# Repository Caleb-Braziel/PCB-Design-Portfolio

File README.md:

# PCB Design Portfolio

This repository contains a curated set of PCB design projects developed for instructional use and technical mentorship. The designs demonstrate practical workflows in schematic capture, hierarchical design, PCB layout, and manufacturability using KiCad and EAGLE.

While many of these projects were created for teaching purposes, they reflect real-world PCB design practices and increasing levels of technical complexity.

---

## Project Overview

The projects in this repository span a range of complexity, from introductory designs to advanced power and embedded systems.

### EAGLE Projects
- **Night Light PCB**  
  A fully fabricated PCB for a night light circuit, including LED and basic power components, laid out and soldered.

### KiCad Projects
- **AC to DC Converter**  
  An AC-DC power supply PCB circuit, designed for voltage conversion and basic power regulation.

- **DC Motor Speed Controller**  
  A PCB for controlling the speed of a DC motor, using discrete components and control circuitry.

- **GPS Tracker with STM32**  
  A microcontroller-based PCB integrating a GPS module for location tracking.

---

## Design Focus

Across these projects, the primary design goals include:
- Clear schematic organization and hierarchy
- Manufacturable PCB layouts
- Proper grounding and power distribution
- Debuggability and clarity for future modification
- Progressive increase in design complexity

---

## Tools & Technologies

- **EDA Tools:** KiCad, EAGLE  
- **Design Skills:** Schematic capture, hierarchical design, PCB layout, ERC/DRC validation  
- **Domains:** Power electronics, motor control, embedded systems  
- **Fabrication:** PCB manufacturing support and hand soldering (select projects)

---

## Notes

Some designs were developed as instructional examples and may not represent finalized commercial products. However, all projects follow industry-standard PCB design practices and are intended to demonstrate technical proficiency and design intent.

---

## Author

Caleb Braziel  
Mechanical Engineering / Embedded & PCB Design

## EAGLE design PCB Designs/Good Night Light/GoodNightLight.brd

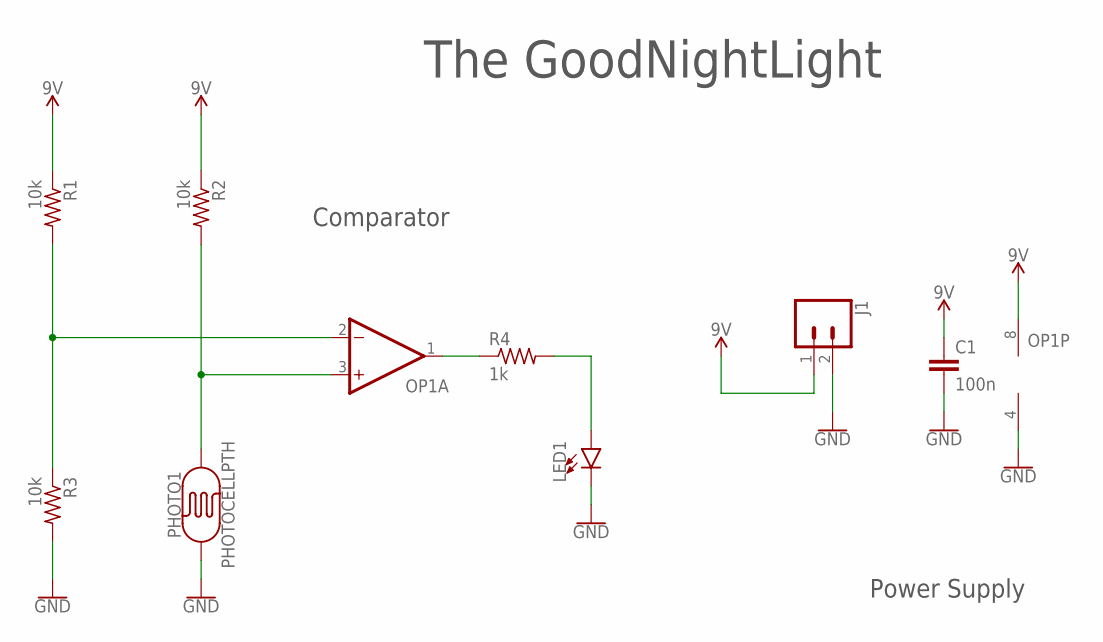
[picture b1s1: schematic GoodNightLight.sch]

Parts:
C1: 100n; C0603
J1: CONN_02; 1X02
LED1: LED5MM; LED_5MM
OP1: OP-DUALR; SO8
PHOTO1: PHOTOCELLPTH; PHOTOCELL
R1, R2, R3: 10k; R0603
R4: 1k; R0603

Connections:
9V: C1.1, J1.1, OP1.8 (V+), R1.1, R2.1
GND: C1.2, J1.2, LED1.K (C), OP1.4 (V-), PHOTO1.1, R3.2
unnamed: OP1.3 (+IN), PHOTO1.2, R2.2
unnamed: OP1.1 (OUT), R4.1
unnamed: OP1.2 (-IN), R1.2, R3.1
unnamed: LED1.A, R4.2

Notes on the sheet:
The GoodNightLight
Comparator
Power Supply

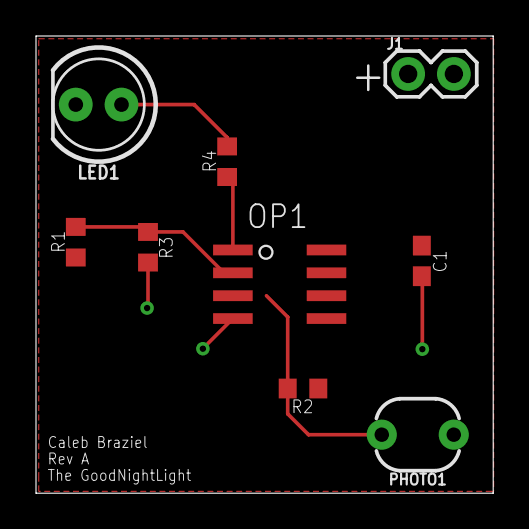
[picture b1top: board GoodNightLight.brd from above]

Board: 2 copper layers, 25.4 x 25.4 mm, 9 parts (0 on the bottom side), 6 nets.
